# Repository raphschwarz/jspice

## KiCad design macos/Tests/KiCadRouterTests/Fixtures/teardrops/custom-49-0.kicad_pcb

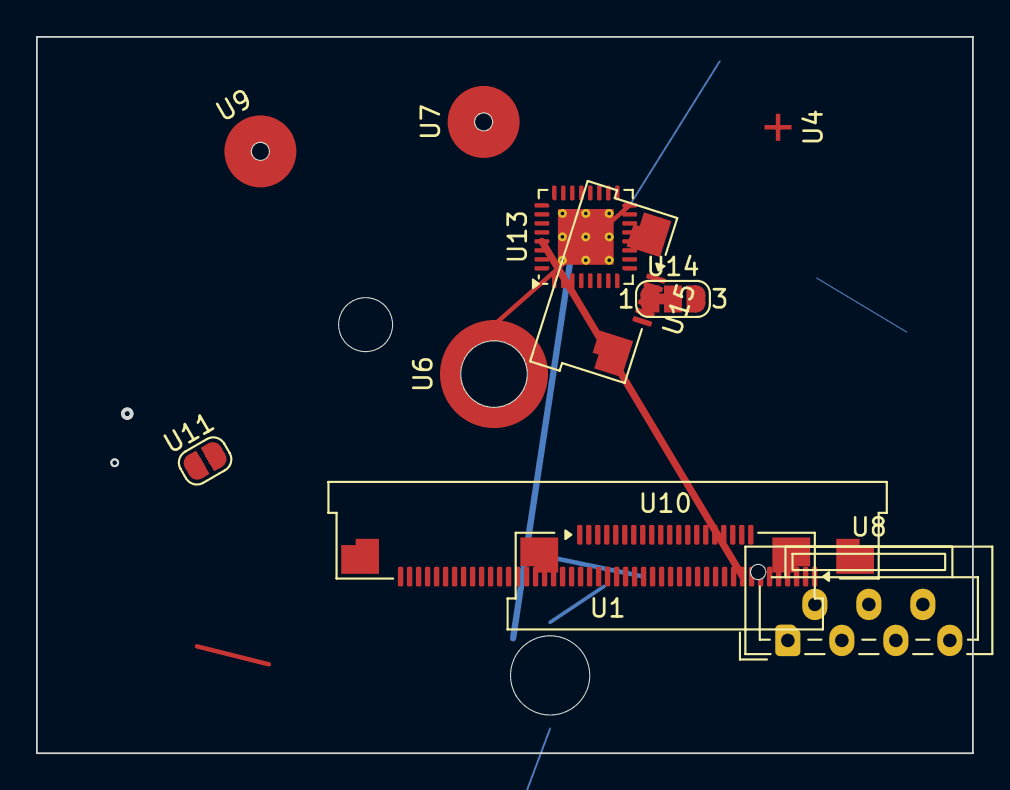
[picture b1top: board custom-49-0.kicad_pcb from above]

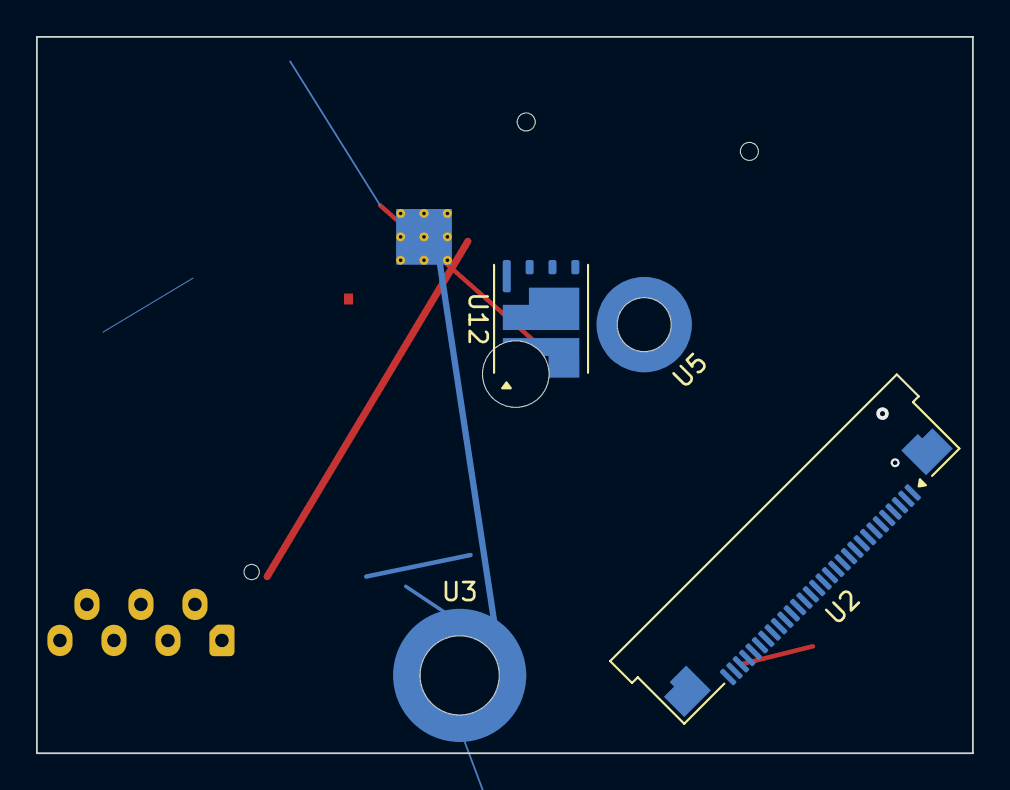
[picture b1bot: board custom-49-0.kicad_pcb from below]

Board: 2 copper layers, 52.0 x 39.8 mm, 15 parts (4 on the bottom side), 13 nets.

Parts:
U1: Amphenol_F32Q-1A7x1-11047_1x47-1MP_P0.5mm_Horizon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; Amphenol_F32Q-1A7x1-11047_1x47-1MP_P0.5mm_Horizontal
U2: Amphenol_F32Q-1A7x1-11030_1x30-1MP_P0.5mm_Horizon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; Amphenol_F32Q-1A7x1-11030_1x30-1MP_P0.5mm_Horizontal
U3: Mounting_Wuerth_WA-SMST-3.3mm_H15mm_9774150960
U4: Fiducial_Cross_1.5mm_Mask2mm
U5: Mounting_Wuerth_WA-SMST-2.25mm_H5mm_9774050943
U6: Mounting_Wuerth_WA-SMST-2.7mm_H10mm_9774100951
U7: Mounting_Wuerth_WA-SMSI-M1.6_H4.5mm_ThreadDepth2m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; Mounting_Wuerth_WA-SMSI-M1.6_H4.5mm_ThreadDepth2mm_97730456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
U8: JST_ZE_B07B-ZESK-1D_1x07_P1.50mm_Vertical
U9: Mounting_Wuerth_WA-SMSI-M1.6_H3.5mm_ThreadDepth2m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; Mounting_Wuerth_WA-SMSI-M1.6_H3.5mm_ThreadDepth2mm_97730356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
U10: Amphenol_F32R-1A7x1-11020_1x20-1MP_P0.5mm_Horizon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; Amphenol_F32R-1A7x1-11020_1x20-1MP_P0.5mm_Horizontal
U11: SolderJumper-2_P1.3mm_Open_RoundedPad1.0x1.5mm
U12: Infineon_PG-TISON-8-4
U13: TQFN-32-1EP_5x5mm_P0.5mm_EP3.1x3.1mm_ThermalVias
U14: SolderJumper-3_P1.3mm_Bridged12_RoundedPad1.0x1.5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; SolderJumper-3_P1.3mm_Bridged12_RoundedPad1.0x1.5mm_NumberL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
U15: Amphenol_F32R-1A7x1-11006_1x06-1MP_P0.5mm_Horizon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; Amphenol_F32R-1A7x1-11006_1x06-1MP_P0.5mm_Horizontal

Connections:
/net3: U1.25, U1.43, U2.3, U2.22, U2.29, U8.3, U9.1, U10.2, U10.14, U12.3, U13.13, U13.16
/sub/clk: U1.10, U2.11, U2.13, U2.28, U10.16, U11.1, U13.8, U13.33
D7: U1.9, U2.17, U8.1, U10.3, U10.4, U12.8, U13.11
D12: U1.4, U1.20, U1.23, U1.29, U2.2, U2.6, U2.14, U2.25, U10.5, U10.MP, U13.9, U13.14, U13.26, U13.33, U15.6
GND: U1.3, U1.18, U1.26, U1.27, U1.28, U5.1, U8.7, U10.17, U13.15, U13.17, U13.19, U13.33, U15.3, U15.MP
N1: U1.21, U2.12, U2.18, U2.24, U3.1, U6.1, U8.4, U10.1, U10.10, U12.4, U13.4, U13.33
N2: U1.1, U1.30, U5.1, U7.1, U8.2, U9.1, U10.9, U10.11, U10.12, U12.2, U13.10, U13.28, U13.33
N3: U1.2, U1.15, U1.37, U2.7, U2.20, U2.MP, U3.1, U7.1, U10.15, U12.1, U13.20, U14.1
PWR1: U1.7, U1.MP, U2.16, U2.21, U8.5, U13.1
PWR_5V: U1.19, U1.41, U1.MP, U2.4, U6.1, U13.12, U13.18, U13.29, U13.30
SIG1: U1.13, U1.22, U1.32, U1.45, U1.46, U2.8, U2.9, U2.26, U13.6, U13.32, U13.33
SIG2: U1.17, U1.31, U1.36, U1.40, U2.5, U2.23, U2.27, U3.1, U5.1, U15.5
VCC: U1.38, U1.42, U2.19, U2.MP, U3.1, U5.1, U9.1, U10.6, U11.2, U13.7, U13.22, U13.25, U13.27, U13.31, U14.2, U15.2, U15.4

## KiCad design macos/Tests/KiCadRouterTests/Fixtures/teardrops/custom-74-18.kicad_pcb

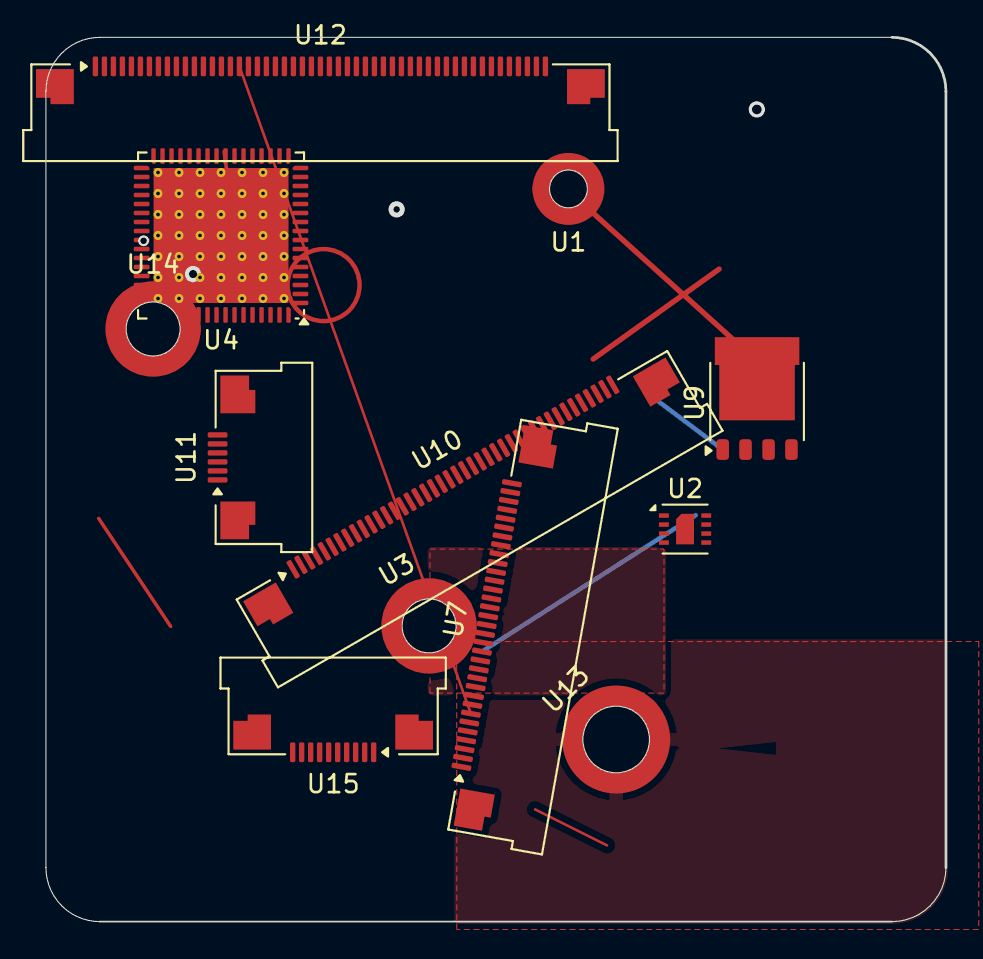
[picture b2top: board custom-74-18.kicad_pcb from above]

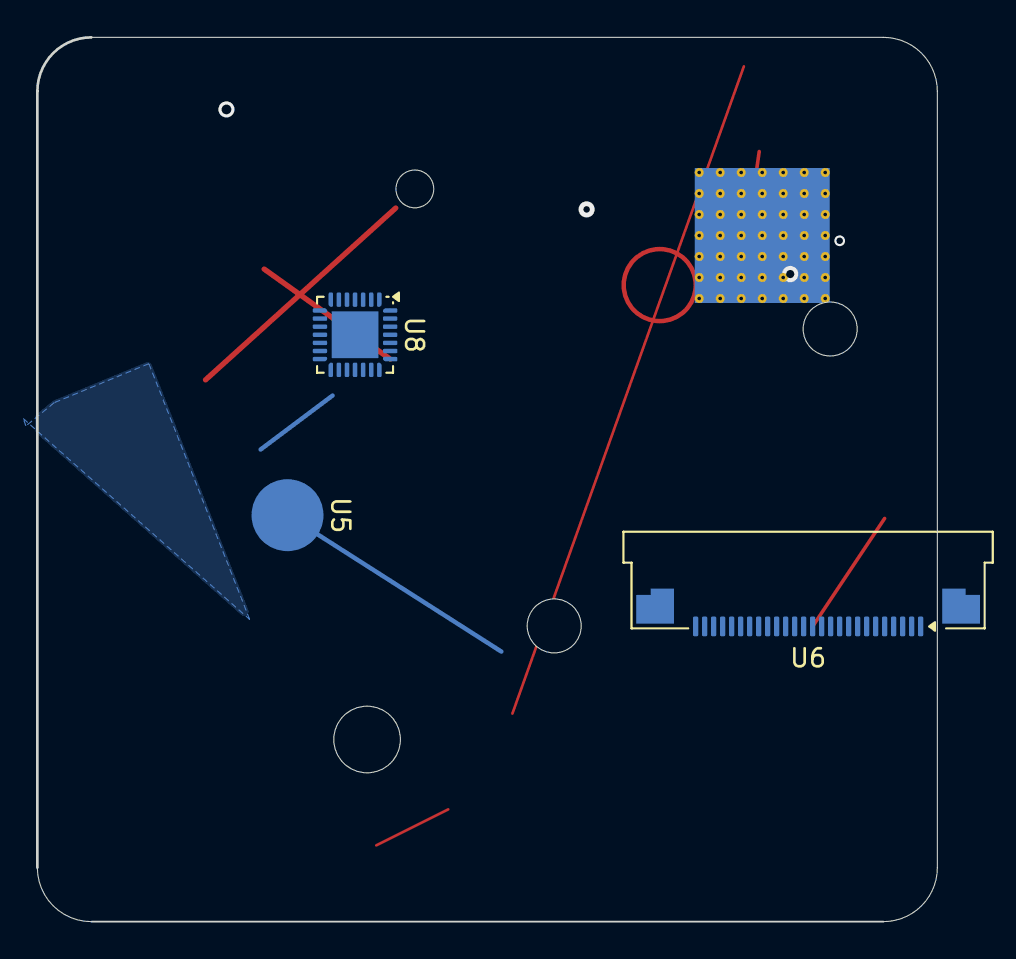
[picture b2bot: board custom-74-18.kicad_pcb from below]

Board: 2 copper layers, 50.0 x 49.1 mm, 15 parts (3 on the bottom side), 6 nets.

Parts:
U1: Mounting_Wuerth_WA-SMSI-M1.6_H0.5mm_9774005633
U2: Sensirion_DFN-8-1EP_2.5x2.5mm_P0.5mm_EP1.1x1.7mm
U3: Mounting_Wuerth_WA-SMSI-M2_H7mm_9774070243
U4: QFN-64-1EP_9x9mm_P0.5mm_EP7.5x7.5mm_ThermalVias
U5: Mounting_Wuerth_WA-SMSI-M1.6_H4mm_ThreadDepth2mm_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; Mounting_Wuerth_WA-SMSI-M1.6_H4mm_ThreadDepth2mm_NoNPTH_977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
U6: Amphenol_F32Q-1A7x1-11026_1x26-1MP_P0.5mm_Horizon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; Amphenol_F32Q-1A7x1-11026_1x26-1MP_P0.5mm_Horizontal
U7: Amphenol_F32Q-1A7x1-11033_1x33-1MP_P0.5mm_Horizon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; Amphenol_F32Q-1A7x1-11033_1x33-1MP_P0.5mm_Horizontal
U8: QFN-28-1EP_4x4mm_P0.45mm_EP2.6x2.6mm
U9: LFPAK56
U10: Amphenol_F32R-1A7x1-11042_1x42-1MP_P0.5mm_Horizon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; Amphenol_F32R-1A7x1-11042_1x42-1MP_P0.5mm_Horizontal
U11: Amphenol_F32R-1A7x1-11006_1x06-1MP_P0.5mm_Horizon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; Amphenol_F32R-1A7x1-11006_1x06-1MP_P0.5mm_Horizontal
U12: Amphenol_F32Q-1A7x1-11051_1x51-1MP_P0.5mm_Horizon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; Amphenol_F32Q-1A7x1-11051_1x51-1MP_P0.5mm_Horizontal
U13: Mounting_Wuerth_WA-SMSI-M2.5_H8.5mm_9774085151
U14: Mounting_Wuerth_WA-SMSI-M2_H8mm_9774080243
U15: Amphenol_F32R-1A7x1-11010_1x10-1MP_P0.5mm_Horizon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; Amphenol_F32R-1A7x1-11010_1x10-1MP_P0.5mm_Horizontal

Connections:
D12: U2.6, U2.8, U3.1, U4.5, U4.29, U4.38, U4.43, U4.54, U4.65, U6.11, U6.18, U6.20, U6.23, U7.10, U7.23, U7.25, U8.2, U8.3, U8.11, U8.21, U9.2, U10.3, U10.11, U10.30, U10.41, U10.42, U11.5, U12.1, U12.2, U12.4, U12.18, U12.20, U12.36, U12.41, U12.47, U13.1
N1: U2.9, U3.1, U4.3, U4.8, U4.12, U4.18, U4.19, U4.21, U4.34, U4.40, U4.48, U4.59, U4.65, U6.5, U6.8, U6.15, U6.MP, U7.4, U7.8, U7.13, U7.16, U7.24, U7.26, U7.27, U8.12, U8.13, U8.14, U8.15, U8.18, U8.20, U8.24, U10.4, U11.4, U12.9, U12.15, U12.21, U12.25, U12.29, U12.33, U12.39, U12.45, U12.48, U12.MP, U13.1, U14.1, U15.2, U15.5, U15.7
PWR_5V: U1.1, U2.7, U4.33, U4.39, U4.44, U4.46, U4.47, U4.52, U4.53, U4.58, U4.65, U6.3, U6.17, U6.21, U7.3, U7.11, U7.12, U7.14, U7.21, U7.31, U7.32, U7.MP, U8.4, U8.7, U10.6, U10.10, U10.22, U10.28, U10.33, U10.34, U10.35, U10.40, U11.3, U11.MP, U12.5, U12.6, U12.11, U12.31, U12.37, U12.44, U12.MP, U13.1, U15.3, U15.6
SIG1: U2.2, U2.4, U4.1, U4.17, U4.28, U4.31, U4.55, U4.63, U4.65, U6.10, U7.2, U7.17, U7.30, U7.33, U7.MP, U8.5, U8.9, U8.16, U10.2, U10.14, U10.16, U10.31, U10.MP, U11.MP, U12.12, U12.17, U12.26, U12.30, U12.43, U14.1, U15.10
SIG2: U1.1, U2.1, U2.3, U4.2, U4.4, U4.10, U4.20, U4.30, U4.32, U4.57, U4.62, U4.65, U6.1, U6.6, U6.9, U7.7, U7.9, U7.15, U7.22, U8.1, U8.22, U8.26, U8.29, U9.4, U10.1, U10.8, U10.29, U10.37, U10.38, U10.39, U10.MP, U12.8, U12.22, U12.40, U12.42, U12.51
VCC: U1.1, U2.5, U4.6, U4.11, U4.25, U4.26, U4.37, U4.49, U4.56, U4.64, U4.65, U6.7, U6.14, U6.22, U6.MP, U7.18, U7.19, U8.6, U8.27, U9.1, U10.15, U10.18, U10.24, U10.25, U10.27, U12.3, U12.13, U12.16, U12.19, U12.49, U13.1, U15.MP

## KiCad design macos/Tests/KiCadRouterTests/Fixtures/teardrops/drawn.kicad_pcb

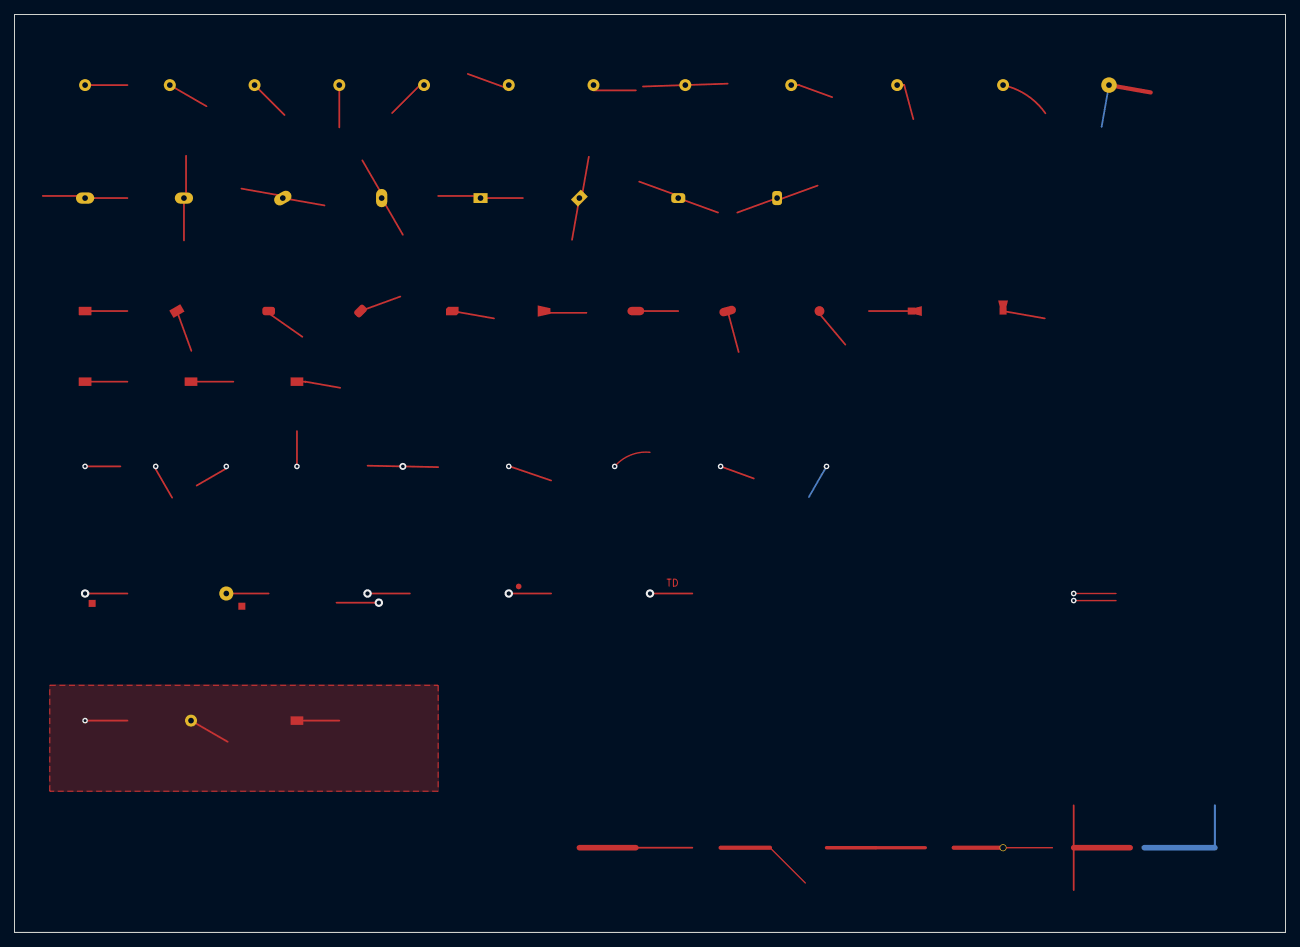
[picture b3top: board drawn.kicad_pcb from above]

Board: 4 copper layers, 180.0 x 130.0 mm, 40 parts (0 on the bottom side), 4 nets.

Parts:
M0, M1, M2, M3, M4, M5, M6, M7, M8, M9, M10: (no value)
N1, N2, N3: (no value)
O0, O1, O2: (no value)
P0, P1, P2, P3, P4, P5, P6, P7: (no value)
R0, R1, R2, R3, R4, R5, R6: (no value)
S1, S2, S3: (no value)
T1: (no value)
W1: (no value)
X1: (no value)
Z1, Z2: (no value)

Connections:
A: P0.1, P1.1, P2.1, P3.1, P4.1, P5.1, P6.1, P7.1, R0.1, R1.1, R2.1, R3.1, R4.1, R5.1, R6.1
B: M0.1, M1.1, M2.1, M3.1, M4.1, M5.1, M6.1, M7.1, M8.1, M9.1, M10.1, N1.1, N2.1, N3.1, S1.1, S2.1, S3.1, X1.1
E: O0.1, O2.1, T1.1
GND: Z1.1, Z2.1

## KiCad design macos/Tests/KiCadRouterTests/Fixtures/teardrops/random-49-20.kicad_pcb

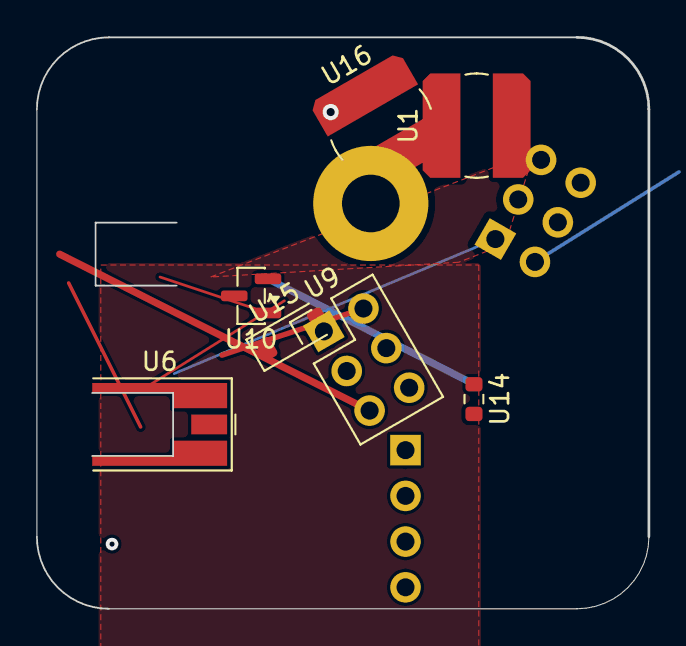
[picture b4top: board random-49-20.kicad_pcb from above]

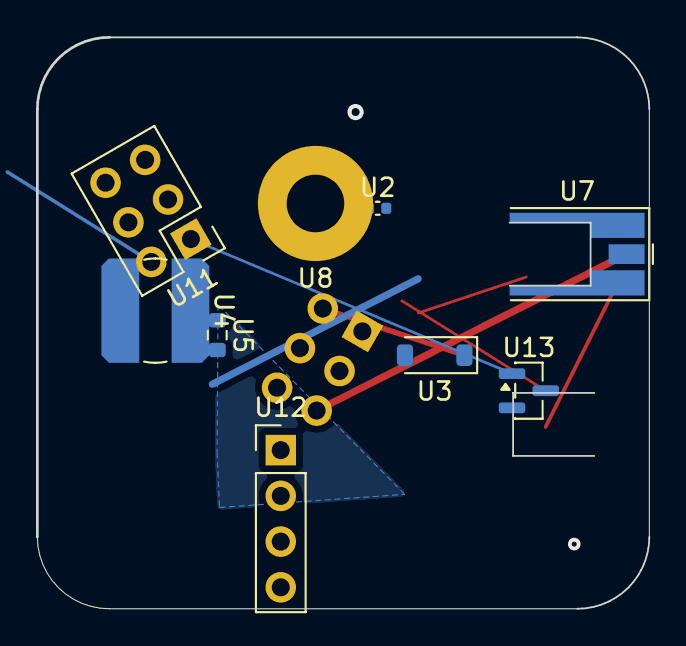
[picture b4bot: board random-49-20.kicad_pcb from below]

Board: 2 copper layers, 34.0 x 31.7 mm, 16 parts (9 on the bottom side), 7 nets.

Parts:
U1, U4, U16: L_Bourns_SDR0604
U2: C_0402_1005Metric
U3, U15: D_SOD-123
U5, U14: R_0603_1608Metric
U6, U7: MMCX_Molex_73415-0961_Horizontal_0.8mm-PCB
U8: MountingHole_3.2mm_M3_Pad
U9, U11: PinHeader_2x03_P2.54mm_Vertical
U10, U13: SOT-23
U12: PinHeader_1x04_P2.54mm_Vertical

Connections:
/net3: U5.2, U9.2, U10.2, U11.3, U14.1
D12: U7.2, U11.1, U11.4, U13.3
GND: U1.2, U9.6, U12.4
N3: U6.1, U7.1, U8.1
PWR1: U10.1, U11.2, U12.3
SIG1: U3.1, U4.1, U9.3, U16.2
VCC: U3.2, U15.2, U16.1

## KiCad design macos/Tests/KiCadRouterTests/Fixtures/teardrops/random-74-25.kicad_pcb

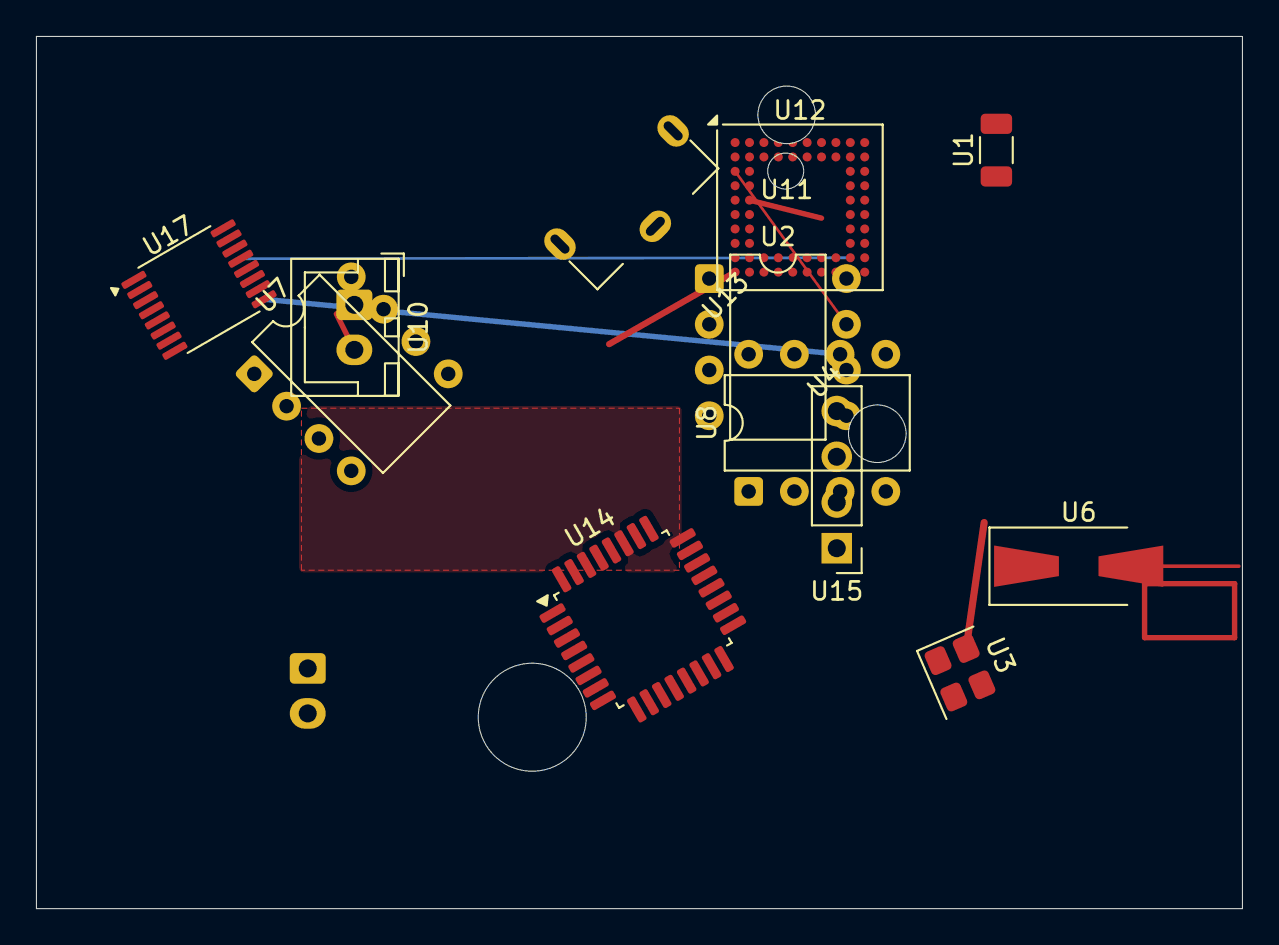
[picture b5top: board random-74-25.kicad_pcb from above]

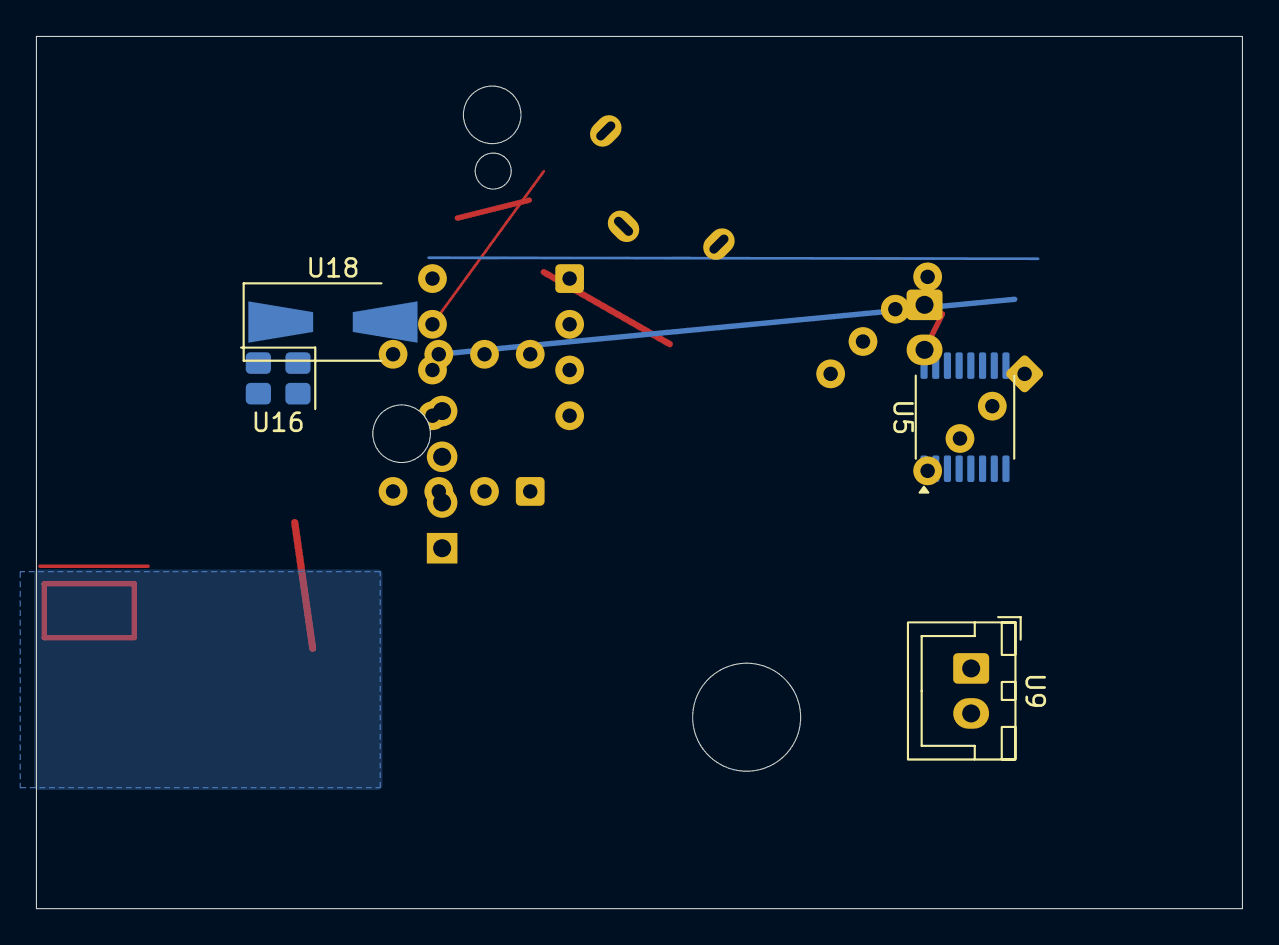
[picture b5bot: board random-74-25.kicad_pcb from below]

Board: 2 copper layers, 67.0 x 48.5 mm, 18 parts (4 on the bottom side), 6 nets.

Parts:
U1: R_1206_3216Metric
U2, U7, U8: DIP-8_W7.62mm
U3, U16: Crystal_SMD_3225-4Pin_3.2x2.5mm
U4, U11: MountingHole_3.2mm_M3
U5, U17: TSSOP-16_4.4x5mm_P0.65mm
U6, U18: D_SMA-SMB_Universal_Handsoldering
U9, U10: JST_XH_B2B-XH-A_1x02_P2.50mm_Vertical
U12: BGA-64_9.0x9.0mm_Layout10x10_P0.8mm
U13: BatteryHolder_Keystone_590
U14: LQFP-32_7x7mm_P0.8mm
U15: PinHeader_1x04_P2.54mm_Vertical

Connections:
/sub/clk: U2.2, U2.3, U5.14, U7.4, U8.8, U9.2, U12.B2, U12.C10, U12.E2, U12.H10, U12.J4, U12.K5, U14.2, U14.11, U14.18, U16.1, U16.2
D7: U1.2, U2.4, U3.1, U5.5, U5.12, U5.13, U7.5, U12.A1, U12.A7, U12.D9, U12.F1, U12.J8, U12.K1, U12.K3, U12.K4, U12.K10, U14.3, U14.5, U14.15, U14.19, U14.26, U14.31, U17.5, U18.2
D12: U2.7, U5.4, U5.9, U5.10, U8.2, U8.5, U8.7, U12.A2, U12.C1, U12.J2, U12.J6, U12.J10, U14.4, U14.7, U14.9, U14.17, U14.22, U14.24, U14.27, U14.30, U17.6, U17.9, U17.11, U17.14
N1: U2.6, U5.3, U6.1, U7.1, U7.7, U7.8, U8.6, U10.2, U12.A4, U12.A9, U12.B1, U12.C2, U12.D10, U12.E1, U12.E9, U12.F10, U12.H1, U12.J1, U12.J5, U12.J9, U12.K6, U13.1, U14.13, U14.23, U14.25, U14.28, U15.1, U16.3, U17.2, U17.15
SIG1: U2.1, U3.3, U5.6, U7.3, U8.3, U8.4, U12.B3, U12.B10, U12.F2, U12.G1, U12.K9, U13.1, U14.1, U14.14, U14.29, U15.4, U16.4, U17.3, U17.4, U17.10
SIG2: U5.2, U5.8, U6.2, U12.A5, U12.A8, U12.B6, U12.D1, U12.H9, U14.12, U14.20, U14.21, U15.2, U17.8, U17.16

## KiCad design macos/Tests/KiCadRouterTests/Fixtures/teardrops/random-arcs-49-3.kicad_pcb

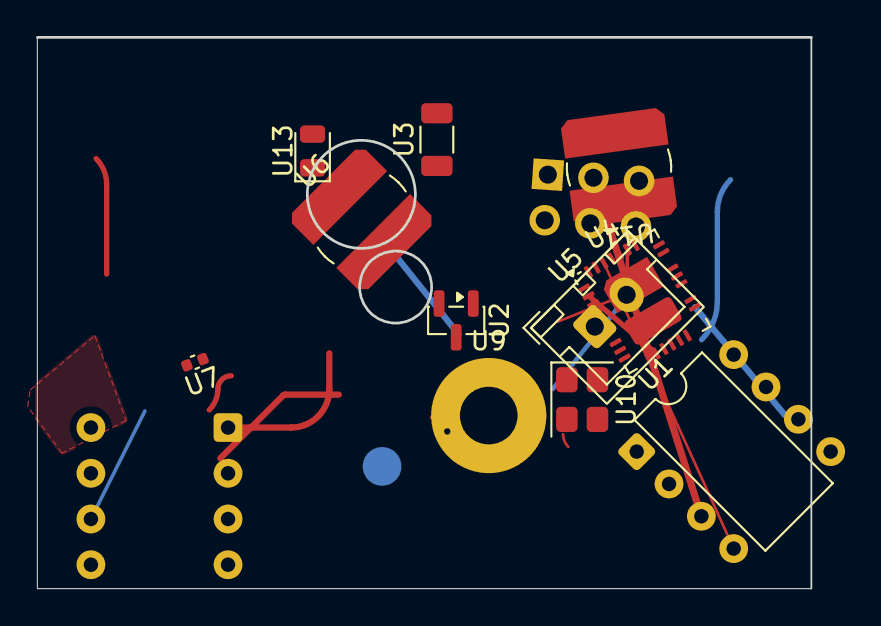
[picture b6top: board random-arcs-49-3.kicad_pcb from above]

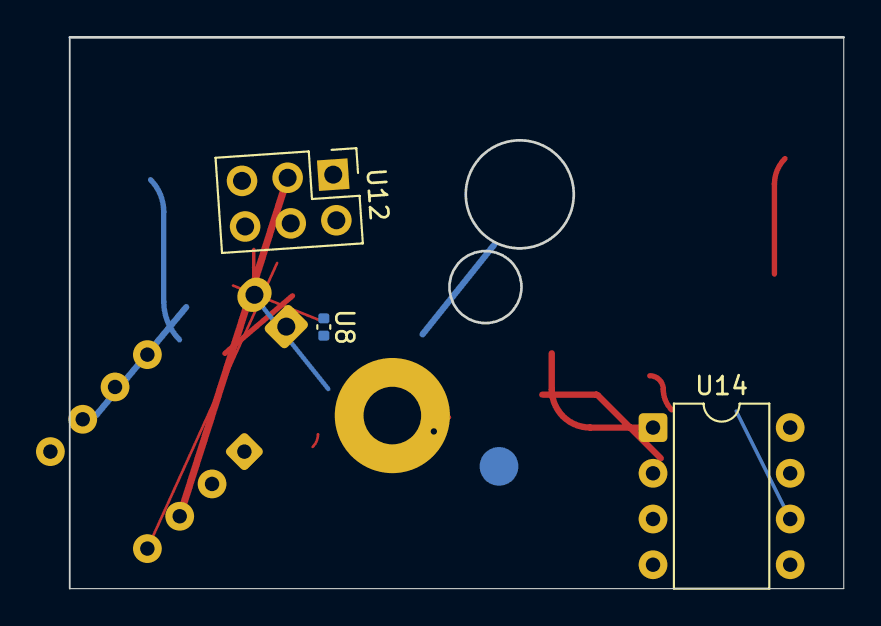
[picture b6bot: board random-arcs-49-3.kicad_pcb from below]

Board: 2 copper layers, 43.0 x 30.6 mm, 14 parts (3 on the bottom side), 7 nets.

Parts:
U1, U14: DIP-8_W7.62mm
U2: SOT-23
U3: R_1206_3216Metric
U4: Analog_QFN-28-36-2EP_5x6mm_P0.5mm
U5: JST_XH_B2B-XH-A_1x02_P2.50mm_Vertical
U6, U11: L_Bourns_SDR0604
U7, U8: C_0402_1005Metric
U9: MountingHole_3.2mm_M3_Pad
U10: Crystal_SMD_3225-4Pin_3.2x2.5mm
U12: PinHeader_2x03_P2.54mm_Vertical
U13: LED_0805_2012Metric

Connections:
/sub/clk: U4.9, U4.23, U4.24, U4.34, U13.2, U14.6
D7: U1.6, U1.7, U3.1, U4.21, U4.30, U4.32, U4.37, U8.2, U12.3, U12.4
D12: U2.1, U4.3, U4.6, U4.8, U4.15, U4.28, U5.2, U7.1, U9.1, U11.1, U12.2, U14.8
N3: U10.1, U12.1
PWR_5V: U1.8, U4.1, U4.12, U4.14, U4.16, U11.2
SIG1: U1.2, U1.4, U4.10, U4.35, U4.36, U4.38, U6.2, U7.2, U8.1, U12.5, U14.1, U14.5, U14.7
VCC: U1.1, U2.2, U4.13, U4.33, U6.1, U10.3, U10.4, U12.6, U14.2
